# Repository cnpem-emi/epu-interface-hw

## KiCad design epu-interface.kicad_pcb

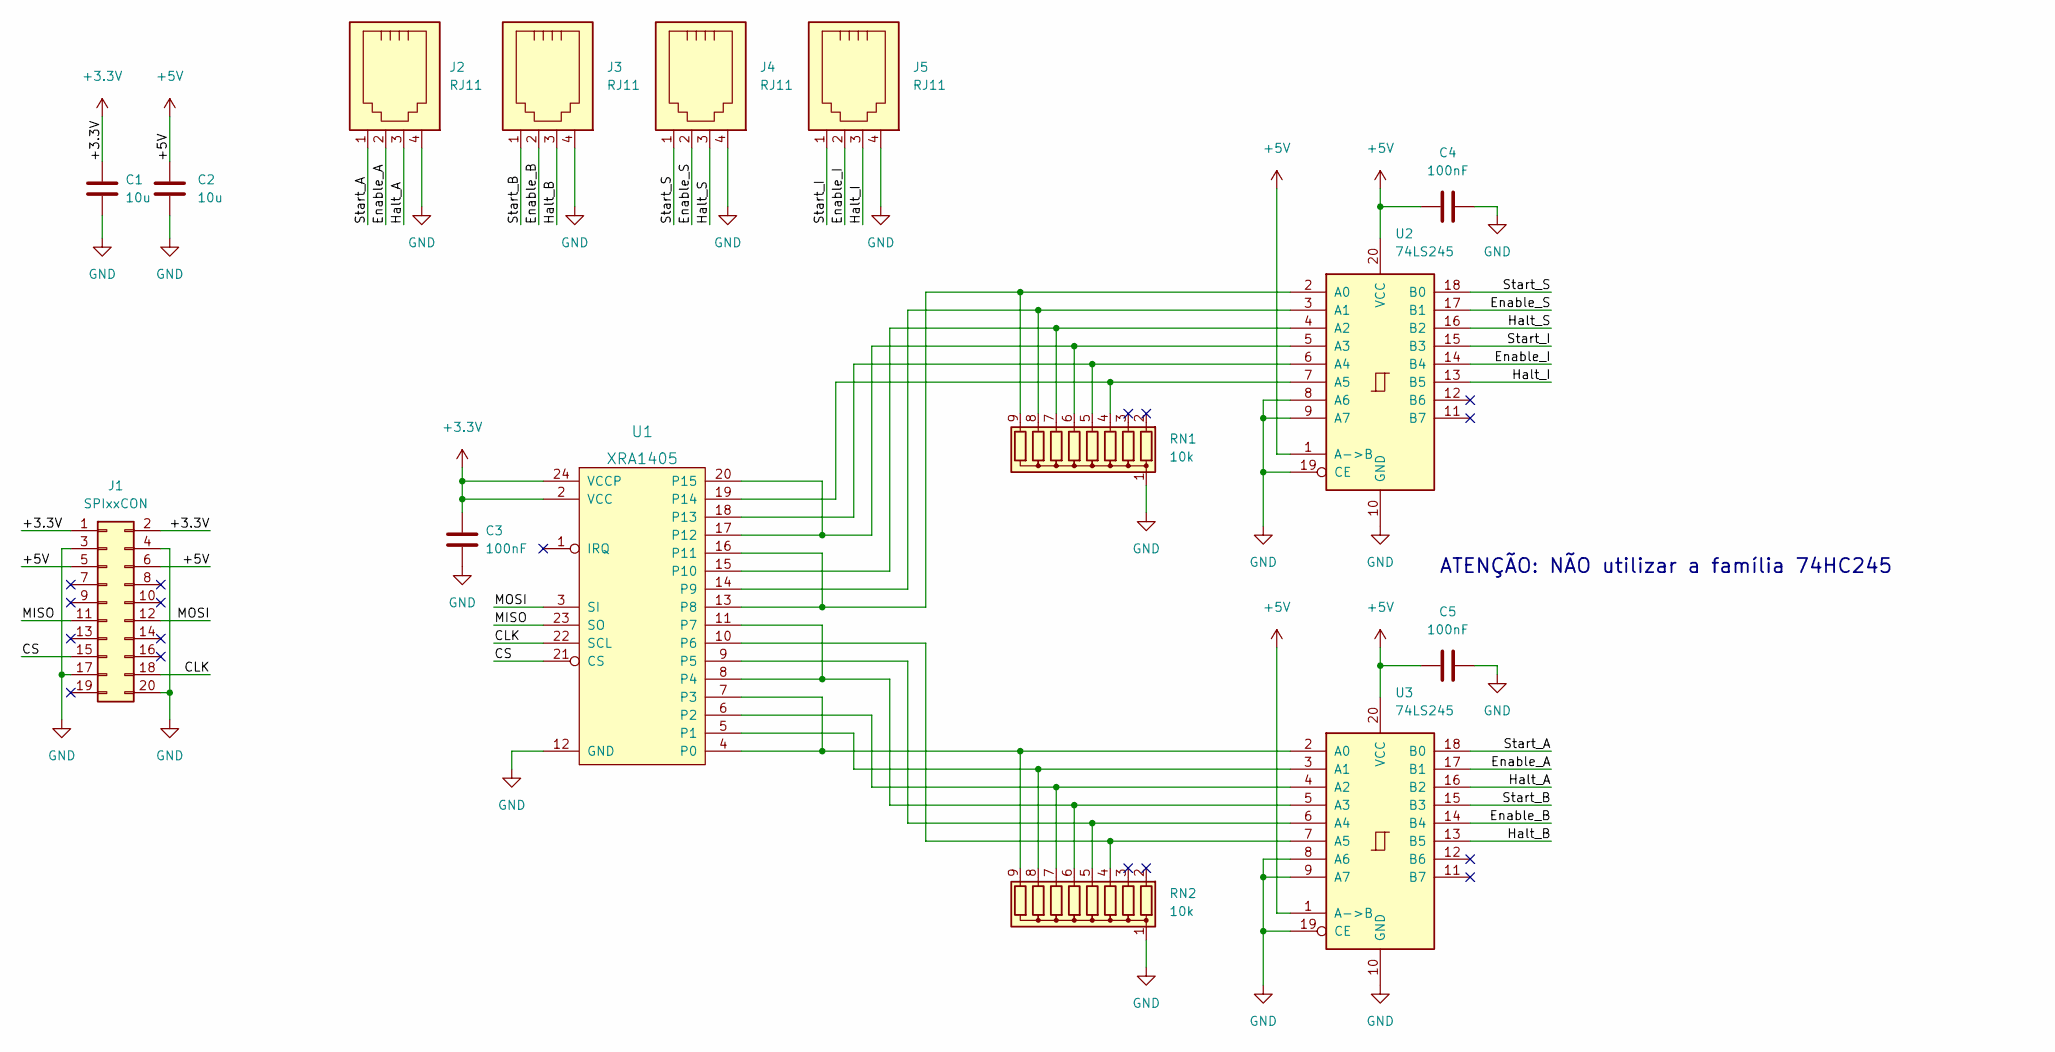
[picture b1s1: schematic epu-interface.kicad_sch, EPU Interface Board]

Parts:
C1, C2: 10u; C_0805_2012Metric
C3, C4, C5: 100nF; C_0805_2012Metric
J1: SPIxxCON; PinHeader_2x10_P2.54mm_Vertical
J2, J3, J4, J5: RJ11; RJ11_2
RN1, RN2: 10k; R_Array_SIP9
U1: XRA1405; TSSOP-24_4.4x7.8mm_P0.65mm
U2, U3: 74LS245; SOIC-20W_7.5x12.8mm_P1.27mm

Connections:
+3V3: C1.1, C3.1, J1.1, J1.2, U1.2 (VCC), U1.24 (VCCP)
+5V: C2.1, C4.2, C5.2, J1.5, J1.6, U2.1 (A->B), U2.20 (VCC), U3.1 (A->B), U3.20 (VCC)
/CLK: J1.18, U1.22 (SCL)
/CS: J1.15, U1.21 (CS)
/Enable_A: J2.2, U3.17 (B1)
/Enable_B: J3.2, U3.14 (B4)
/Enable_I: J5.2, U2.14 (B4)
/Enable_S: J4.2, U2.17 (B1)
/Halt_A: J2.3, U3.16 (B2)
/Halt_B: J3.3, U3.13 (B5)
/Halt_I: J5.3, U2.13 (B5)
/Halt_S: J4.3, U2.16 (B2)
/MISO: J1.11, U1.23 (SO)
/MOSI: J1.12, U1.3 (SI)
/Start_A: J2.1, U3.18 (B0)
/Start_B: J3.1, U3.15 (B3)
/Start_I: J5.1, U2.15 (B3)
/Start_S: J4.1, U2.18 (B0)
GND: C1.2, C2.2, C3.2, C4.1, C5.1, J1.3, J1.4, J1.17, J1.20, J2.4, J3.4, J4.4, J5.4, RN1.1 (common), RN2.1 (common), U1.12 (GND), U2.8 (A6), U2.9 (A7), U2.10 (GND), U2.19 (CE), U3.8 (A6), U3.9 (A7), U3.10 (GND), U3.19 (CE)
unnamed: RN1.4 (R3), U1.19 (P14), U2.7 (A5)
unnamed: RN1.5 (R4), U1.18 (P13), U2.6 (A4)
unnamed: RN1.6 (R5), U1.17 (P12), U1.20 (P15), U2.5 (A3)
unnamed: RN1.7 (R6), U1.15 (P10), U2.4 (A2)
unnamed: RN1.8 (R7), U1.14 (P9), U2.3 (A1)
unnamed: RN1.9 (R8), U1.13 (P8), U1.16 (P11), U2.2 (A0)
unnamed: RN2.4 (R3), U1.10 (P6), U3.7 (A5)
unnamed: RN2.5 (R4), U1.9 (P5), U3.6 (A4)
unnamed: RN2.6 (R5), U1.8 (P4), U1.11 (P7), U3.5 (A3)
unnamed: RN2.7 (R6), U1.6 (P2), U3.4 (A2)
unnamed: RN2.8 (R7), U1.5 (P1), U3.3 (A1)
unnamed: RN2.9 (R8), U1.4 (P0), U1.7 (P3), U3.2 (A0)

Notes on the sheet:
ATENÇÃO: NÃO utilizar a família 74HC245

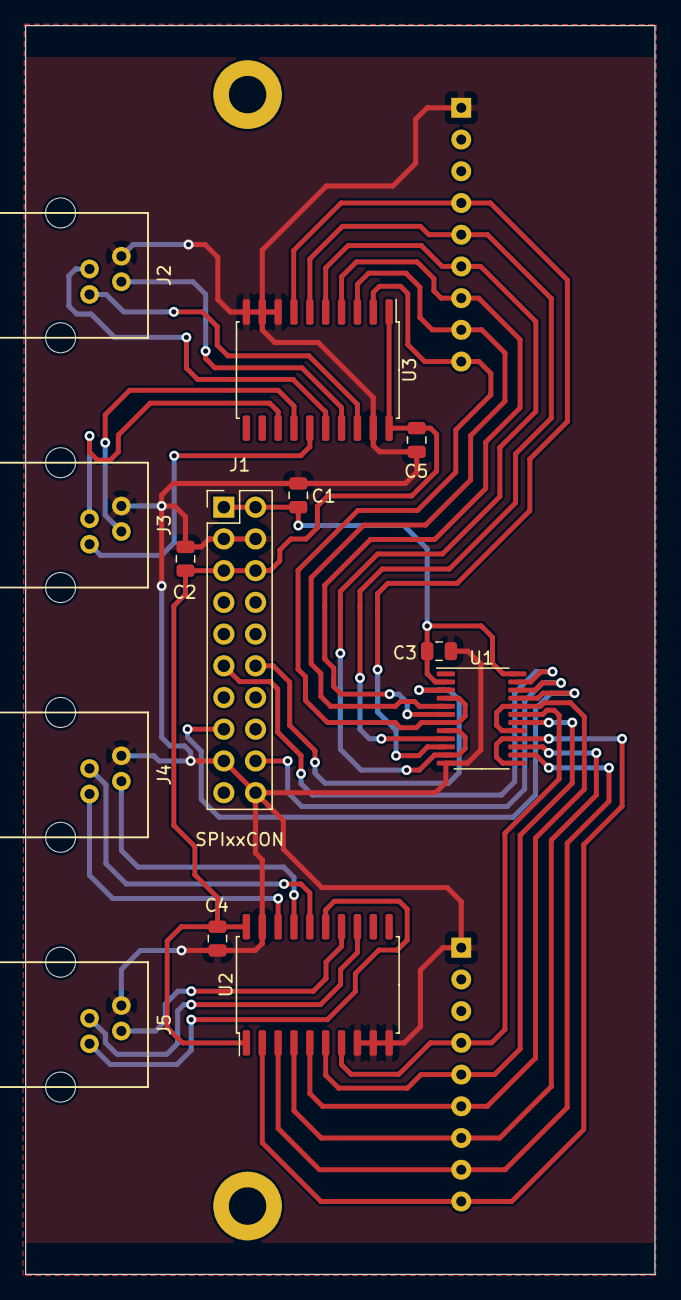
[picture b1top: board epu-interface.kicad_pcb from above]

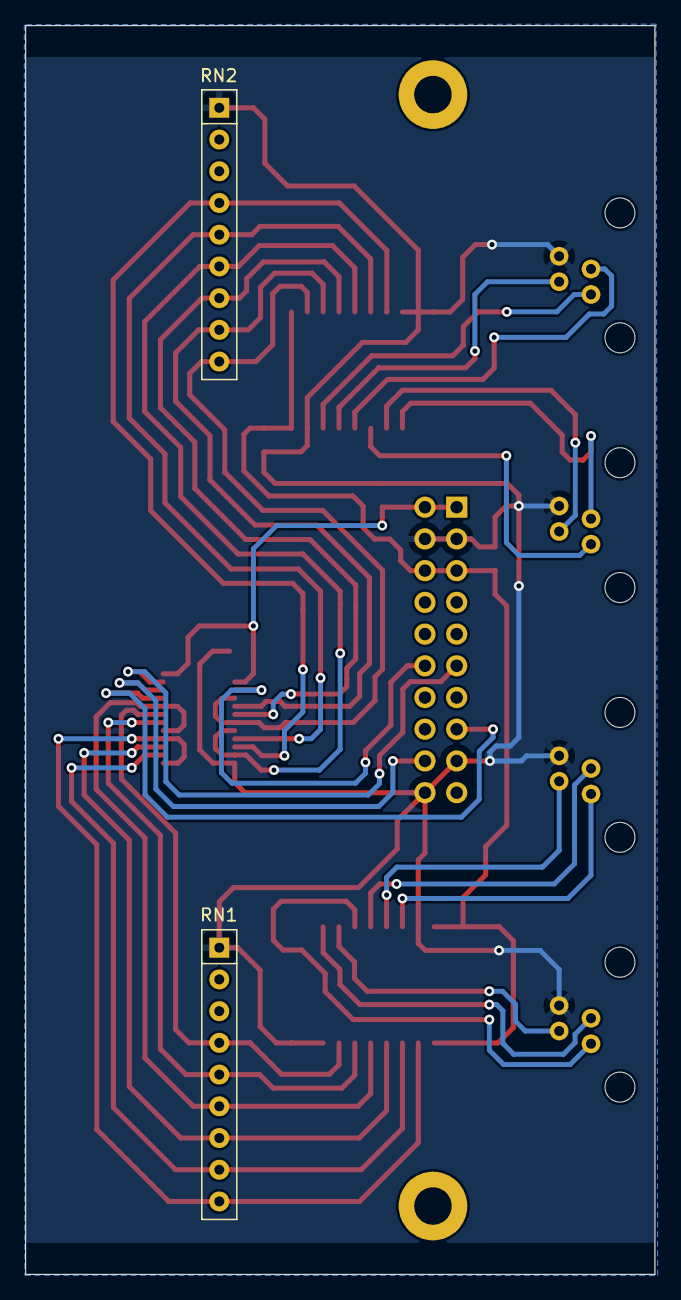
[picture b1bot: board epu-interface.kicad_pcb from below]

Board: 2 copper layers, 50.4 x 100.0 mm, 15 parts (2 on the bottom side), 31 nets.

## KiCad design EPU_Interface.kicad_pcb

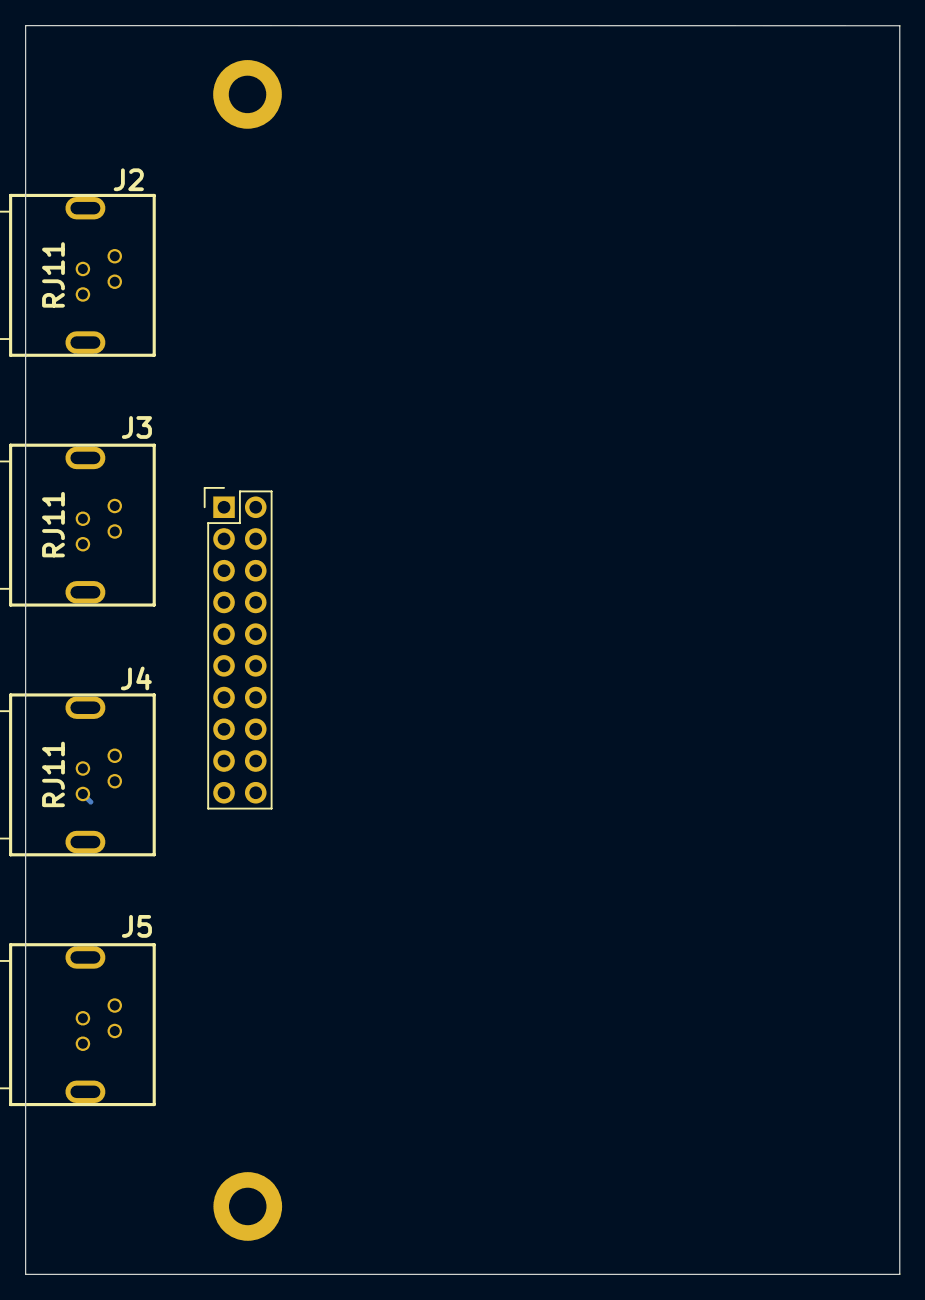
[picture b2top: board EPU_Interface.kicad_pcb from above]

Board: 2 copper layers, 70.0 x 100.0 mm, 5 parts (0 on the bottom side), 4 nets.

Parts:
J1: SPIxxCON; Pin_Header_Straight_2x10
J2, J3, J4, J5: RJ11; RJ11-4P4C-HIROSE

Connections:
+3.3VP: J1.1, J1.2
+5V: J1.5, J1.6
/GND: J2.3, J3.3, J4.3, J5.3
GND: J1.3, J1.4, J1.17, J1.20

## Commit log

2022-10-07 Changed Kicad version compatibilities
2022-10-10 Changed 74HC245 to 74LS245
2022-10-13 Panel
2022-10-19 Added pcb layout
